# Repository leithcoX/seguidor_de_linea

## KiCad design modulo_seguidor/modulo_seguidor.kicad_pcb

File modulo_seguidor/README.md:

# Modulo Seguidor

Este módulo ejecuta las funciones propias de un seguidor de línea, procesar las lecturas del módulo sensor, e integra el puente H L298N para dirigir los motores.

Vista previa de la placa desde arriba

Vista previa de la placa desde abajo

## Diagrama

El diseño está pensado para hacer la PCB de un solo lado, por lo que las pistas rojas tendrán que reemplazarse con cables.

## TODOs
 - Revisar los footprints de las resistencias y de los capacitores
 - Exportar a un modelo 3D (opcional)
 - ~~Probar en placa separada el modulo puente H~~

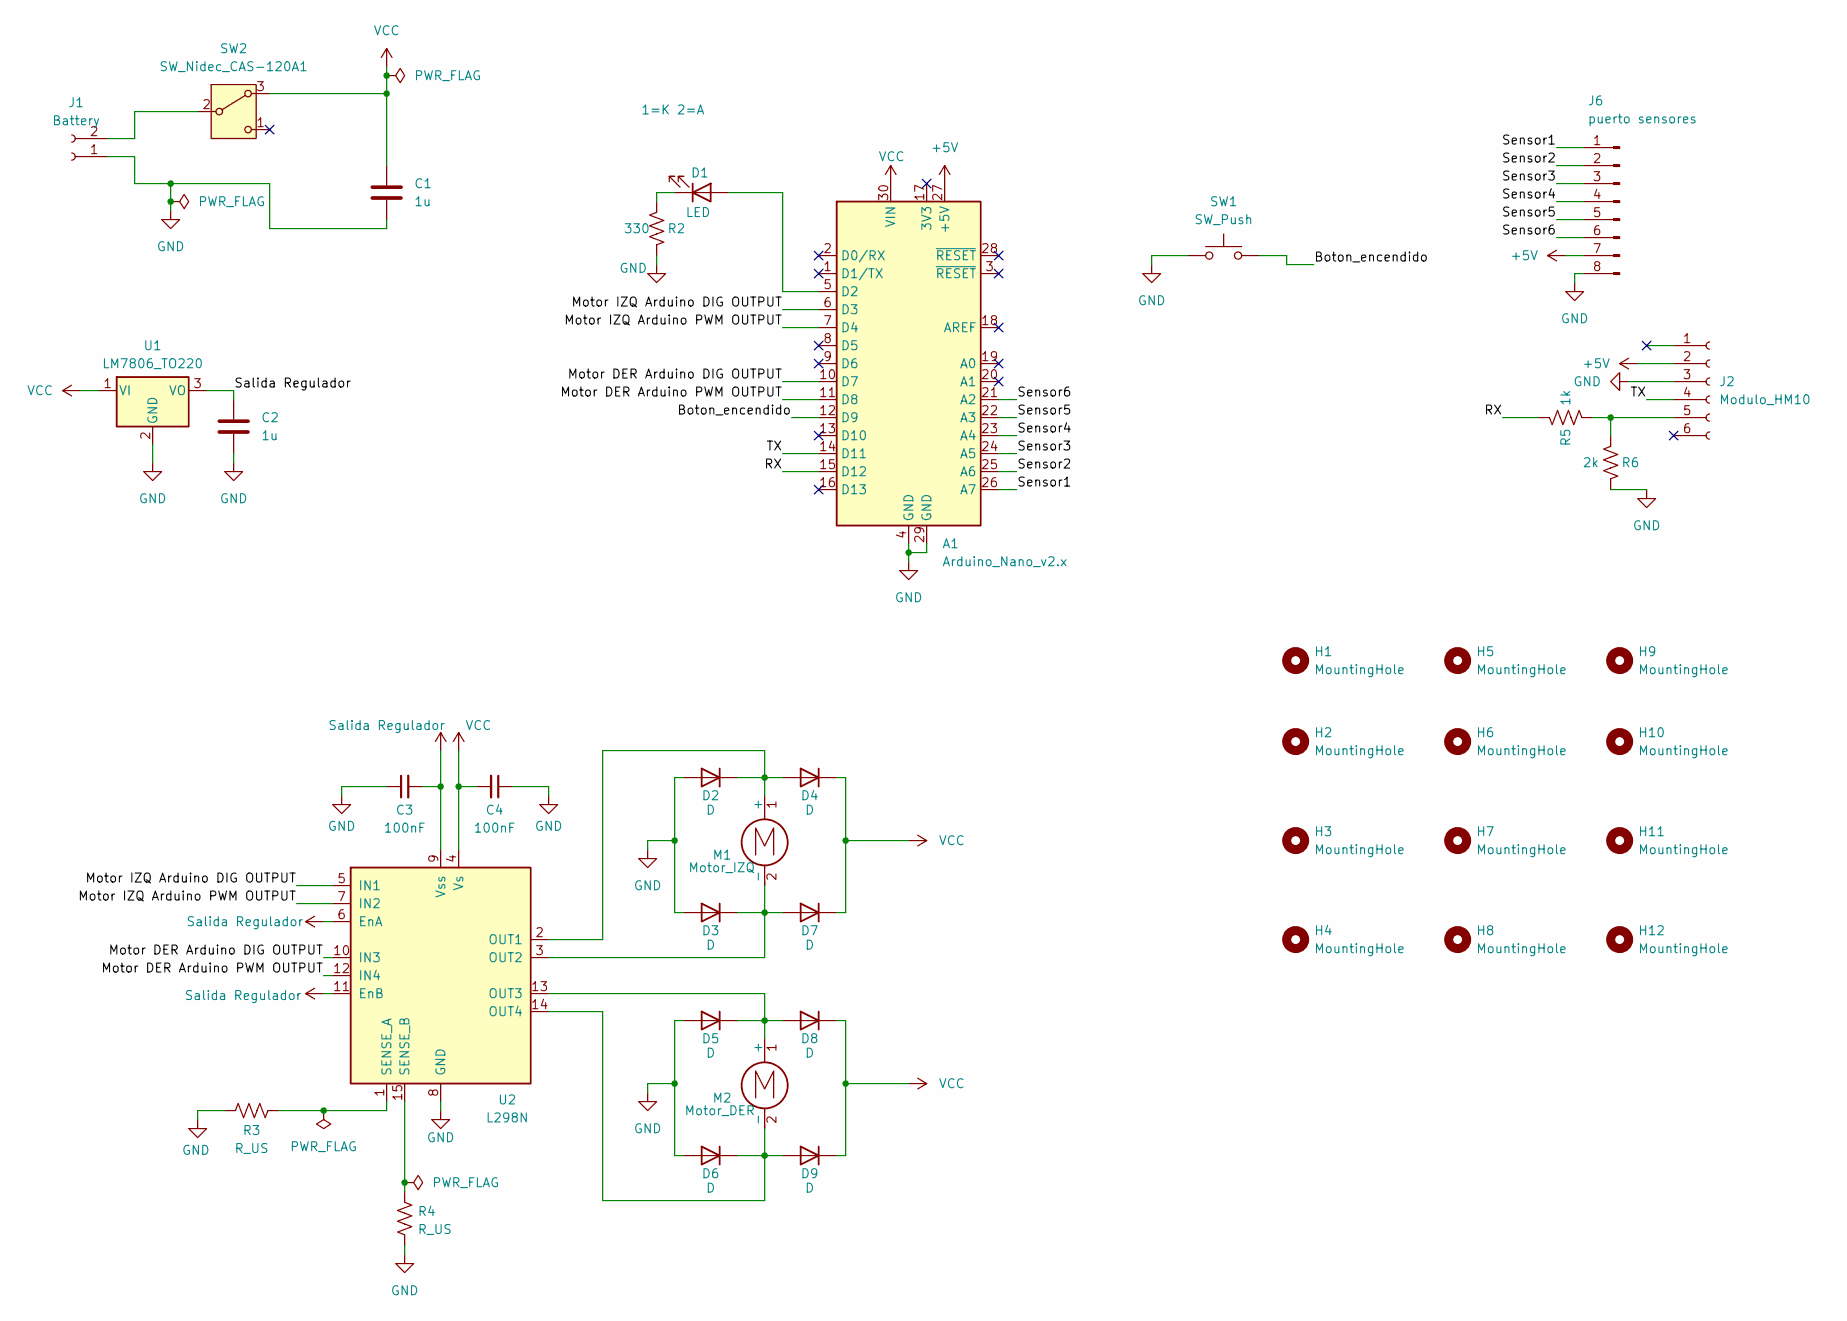
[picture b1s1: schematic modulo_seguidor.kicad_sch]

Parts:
A1: Arduino_Nano_v2.x; Arduino_Nano
C1, C2: 1u; C_1206_3216Metric_Pad1.33x1.80mm_HandSolder
C3, C4: 100nF; C_1206_3216Metric_Pad1.33x1.80mm_HandSolder
D1: LED; LED_D5.0mm
D2, D3, D4, D5, D6, D7, D8, D9: D; D_DO-41_SOD81_P7.62mm_Horizontal
H1, H2, H3, H4, H5, H6, H7, H8, H9, H10, H11, H12: MountingHole; MountingHole_3.2mm_M3
J1: Battery; Molex_KK-254_AE-6410-02A_1x02_P2.54mm_Vertical
J2: Modulo_HM10; PinSocket_1x06_P2.54mm_Vertical
J6: puerto sensores; PinSocket_1x08_P2.54mm_Horizontal
M1: Motor_IZQ; Molex_KK-254_AE-6410-02A_1x02_P2.54mm_Vertical
M2: Motor_DER; Molex_KK-254_AE-6410-02A_1x02_P2.54mm_Vertical
R2: 330; R_1206_3216Metric_Pad1.30x1.75mm_HandSolder
R3, R4: R_US; R_Axial_DIN0207_L6.3mm_D2.5mm_P10.16mm_Horizontal
R5: 1k; R_1206_3216Metric_Pad1.30x1.75mm_HandSolder
R6: 2k; R_1206_3216Metric_Pad1.30x1.75mm_HandSolder
SW1: SW_Push; SW_PUSH_6mm_H5mm
SW2: SW_Nidec_CAS-120A1; SolderWire-0.5sqmm_1x03_P4.6mm_D0.9mm_OD2.1mm
U1: LM7806_TO220; TO-220-3_Vertical
U2: L298N; TO-220-15_P2.54x5.08mm_StaggerOdd_Lead4.58mm_Vertical

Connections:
+5V: A1.27 (+5V), J2.2, J6.7
/Boton_encendido: A1.12 (D9), SW1.2
/Motor DER Arduino DIG OUTPUT: A1.10 (D7), U2.10 (IN3)
/Motor DER Arduino PWM OUTPUT: A1.11 (D8), U2.12 (IN4)
/Motor IZQ Arduino DIG OUTPUT: A1.6 (D3), U2.5 (IN1)
/Motor IZQ Arduino PWM OUTPUT: A1.7 (D4), U2.7 (IN2)
/RX: A1.15 (D12), R5.2
/Sensor1: A1.26 (A7), J6.1
/Sensor2: A1.25 (A6), J6.2
/Sensor3: A1.24 (A5), J6.3
/Sensor4: A1.23 (A4), J6.4
/Sensor5: A1.22 (A3), J6.5
/Sensor6: A1.21 (A2), J6.6
/TX: A1.14 (D11), J2.4
GND: A1.4 (GND), A1.29 (GND), C1.2, C2.2, C3.1, C4.1, D2.2 (A), D3.2 (A), D5.2 (A), D6.2 (A), J1.1, J2.3, J6.8, R2.2, R3.2, R4.1, R6.2, SW1.1, U1.2 (GND), U2.8 (GND)
unnamed: A1.5 (D2), D1.2 (A)
unnamed: D1.1 (K), R2.1
unnamed: D2.1 (K), D4.2 (A), M1.1 (+), U2.2 (OUT1)
unnamed: D3.1 (K), D7.2 (A), M1.2 (-), U2.3 (OUT2)
unnamed: D5.1 (K), D8.2 (A), M2.1 (+), U2.13 (OUT3)
unnamed: D6.1 (K), D9.2 (A), M2.2 (-), U2.14 (OUT4)
unnamed: J1.2, SW2.2 (B)
unnamed: J2.5, R5.1, R6.1
unnamed: R3.1, U2.1 (SENSE_A)
unnamed: R4.2, U2.15 (SENSE_B)
Salida Regulador: C2.1, C3.2, U1.3 (VO), U2.6 (EnA), U2.9 (Vss), U2.11 (EnB)
VCC: A1.30 (VIN), C1.1, C4.2, D4.1 (K), D7.1 (K), D8.1 (K), D9.1 (K), SW2.3 (A), U1.1 (VI), U2.4 (Vs)

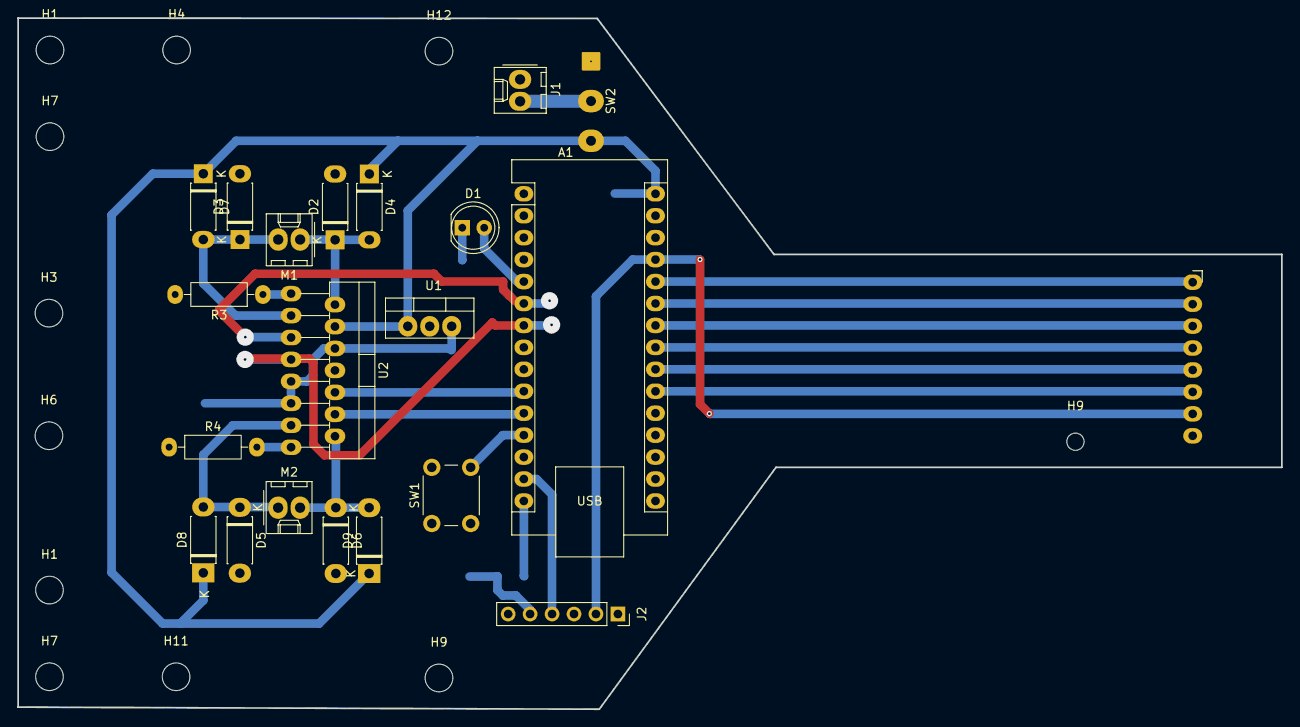
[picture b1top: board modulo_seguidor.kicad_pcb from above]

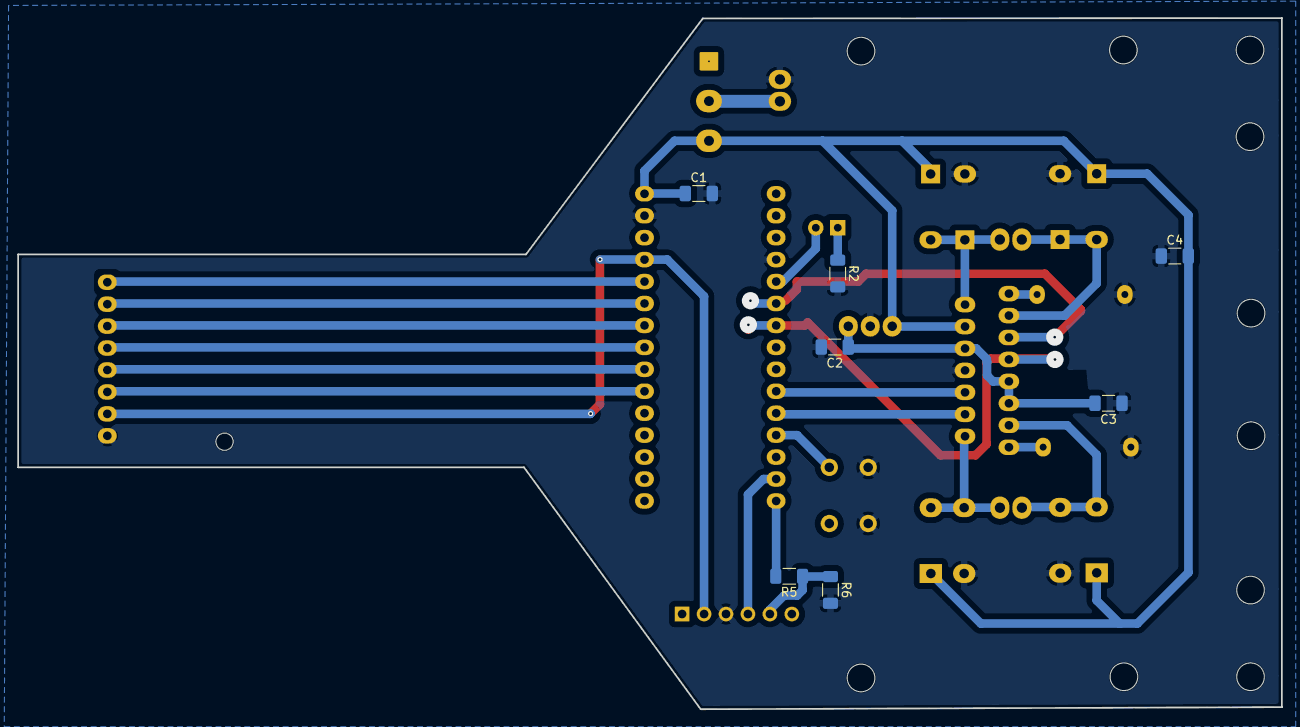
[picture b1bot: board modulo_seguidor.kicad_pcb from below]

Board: 2 copper layers, 146.3 x 80.0 mm, 39 parts (7 on the bottom side), 27 nets.

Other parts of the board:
H1#2, H7#2, H9#2: MountingHole; MountingHole_3.2mm_M3
